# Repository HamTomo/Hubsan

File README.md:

# Hubsan

Hubsan Notes

------------------------------------------------------------
WIP:
-----
- 
- 

------------------------------------------------------------
To Do:
-----
- How does TX/RX pair?
- What is sent over TX?
- What is sent between RX and MCU?
- What are Antennae designs?
- Layout PCBA
- Sniff points
	+ I2C line
	+ SPI line
	+ SDR
- Laptop driven TX

------------------------------------------------------------

------------------------------------------------------------
Done:
-----
- RX Schematic Drawn
- EBoM First Pass

------------------------------------------------------------

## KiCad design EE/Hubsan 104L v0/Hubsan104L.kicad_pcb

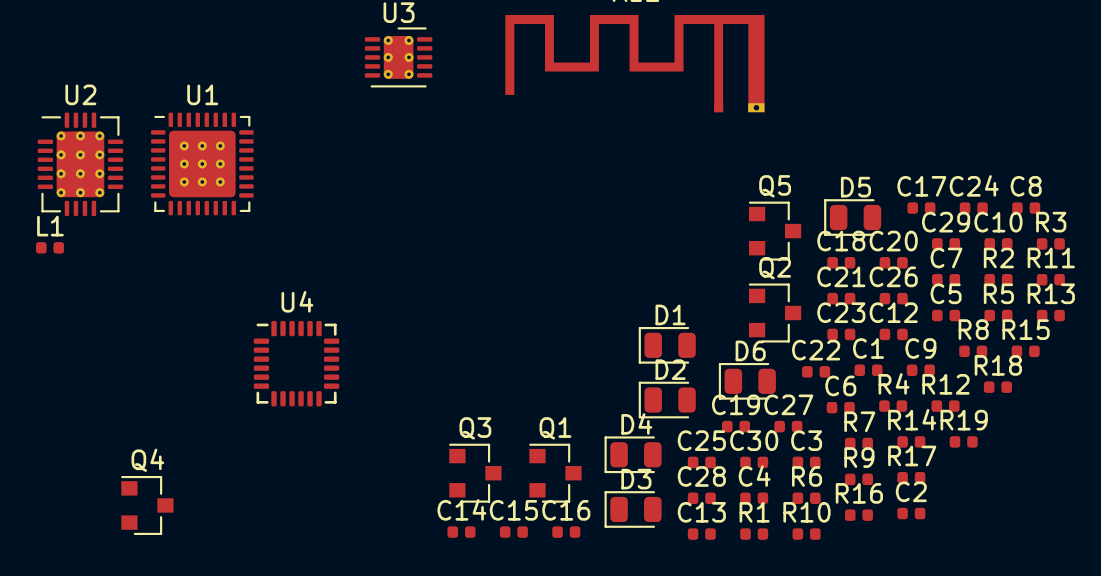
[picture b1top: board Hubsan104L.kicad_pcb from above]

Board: 2 copper layers, 65 parts (0 on the bottom side), 50 nets, no tracks yet.

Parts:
AE1: Antenna; Texas_SWRA117D_2.4GHz_Left
C1, C2, C3, C5, C6, C15, C18, C19, C23, C25, C26, C27, C30: 100nF; C_0402_1005Metric
C4, C13: 1uF; C_0402_1005Metric
C7: 120pF; C_0402_1005Metric
C8: 1.5nF; C_0402_1005Metric
C9: 27pF; C_0402_1005Metric
C10: 12pF; C_0402_1005Metric
C12: 100pF; C_0402_1005Metric
C14: 10pF; C_0402_1005Metric
C16: 680pF; C_0402_1005Metric
C17, C21: 33pF; C_0402_1005Metric
C20, C24: 10nF; C_0402_1005Metric
C22: 8.2uF; C_0402_1005Metric
C28: 2.2nF; C_0402_1005Metric
C29: 10uF; C_0402_1005Metric
D1, D2, D3, D4, D5, D6: LED_Small; LED_0805_2012Metric
L1: 130nH; L_0402_1005Metric
Q1, Q2, Q3, Q4: MTN2310N3; SOT-23
Q5: MCP1700-3002E_SOT23; SOT-23
R1, R2, R6, R12, R13, R16, R17, R18: 10; R_0402_1005Metric
R3: 100; R_0402_1005Metric
R4, R7, R11, R14, R15, R19: 4.7k; R_0402_1005Metric
R5, R8, R10: 10k; R_0402_1005Metric
R9: 200; R_0402_1005Metric
U1: Nuvoton_MINI54ZAN_MCU; QFN-32-1EP_5x5mm_P0.5mm_EP3.7x3.7mm_ThermalVias
U2: Amicom_A7105_TX; QFN-20-1EP_4x5mm_P0.5mm_EP2.65x3.65mm_ThermalVias
U3: MC3210; DFN-10-1EP_3x3mm_P0.5mm_EP1.65x2.38mm_ThermalVias
U4: MPU-6050; InvenSense_QFN-24_4x4mm_P0.5mm

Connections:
+3V0: C1.2, C2.2, C19.1, C29.2, Q5.2, R1.1, R2.1, R12.2, R13.1, R16.1, R17.2, R18.1, U1.28, U2.19, U3.10
+BATT: C3.1, C6.1, C22.1, C25.1, C30.2, Q5.3, R10.2
/B: C21.1, U2.8
/D: C17.1, U2.9
/GYRO_INT: U1.9, U4.12
/INTN: U1.6, U3.5
/LED1_4: D1.1, D4.1, U1.24
/LED2_3: D2.1, D3.1, U1.3
/LED5: R6.2, U1.13
/LED6: R3.2, U1.18
/MOTOR1: Q2.1, R7.1, U1.16
/MOTOR2: Q3.1, R11.1, U1.15
/MOTOR3: Q1.1, R4.1, U1.17
/MOTOR4: Q4.1, R14.1, U1.14
/TX_CKO: R5.1, U2.18
/U1_1: C15.2, R8.1, R10.1, U1.1
/U1_SCL: R19.1, U1.8, U3.7, U4.23
/U1_SDA: R15.1, U1.7, U3.8, U4.24
GND: C1.1, C2.1, C4.1, C5.1, C7.1, C8.1, C12.2, C13.2, C14.2, C15.1, C16.2, C17.2, C18.2, C19.2, C20.2, C21.2, C22.2, C23.2, C24.2, C26.2, C27.1, C28.1, C29.1, D5.1, D6.1, Q1.3, Q2.3, Q3.3, Q4.3, Q5.1, R4.2, R7.2, R8.2, R11.2, R14.2, R15.2, R19.2, U1.12, U2.7, U2.15, U3.4, U3.9, U4.9, U4.11, U4.18
unnamed: AE1.1, C9.2, C10.2
unnamed: C3.2, Q2.2
unnamed: C5.2, U2.13
unnamed: C6.2, Q1.2
unnamed: C7.2, U2.1
unnamed: C8.2, U2.2
unnamed: C9.1, U2.3
unnamed: C10.1, L1.2, U2.4
unnamed: C4.2, C12.1, C13.1, L1.1, U2.10, U2.20
unnamed: C14.1, U2.5
unnamed: C16.1, R9.1, U2.6
unnamed: C18.1, U1.2
unnamed: C20.1, R9.2
unnamed: C23.1, R13.2, U3.3
unnamed: C24.1, R12.1, U4.8
unnamed: C25.2, Q3.2
unnamed: C26.1, U4.10
unnamed: C27.2, R18.2, U4.13
unnamed: C28.2, U4.20
unnamed: C30.1, Q4.2
unnamed: D1.2, R2.2
unnamed: D2.2, R17.1
unnamed: D3.2, R16.2
unnamed: D4.2, R1.2
unnamed: D5.2, R6.1
unnamed: D6.2, R3.1
unnamed: R5.2, U1.11
unnamed: U1.29, U2.16
unnamed: U1.30, U2.14
unnamed: U1.31, U2.12
unnamed: U1.32, U2.11

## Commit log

2021-12-19 Add files
2021-12-19 Combine files
